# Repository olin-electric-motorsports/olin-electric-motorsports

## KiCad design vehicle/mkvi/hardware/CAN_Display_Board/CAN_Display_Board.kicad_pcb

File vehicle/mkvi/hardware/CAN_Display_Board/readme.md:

This repository contains the kicad files for the CAN Display Board that Ian, Peter, and Ahan created.

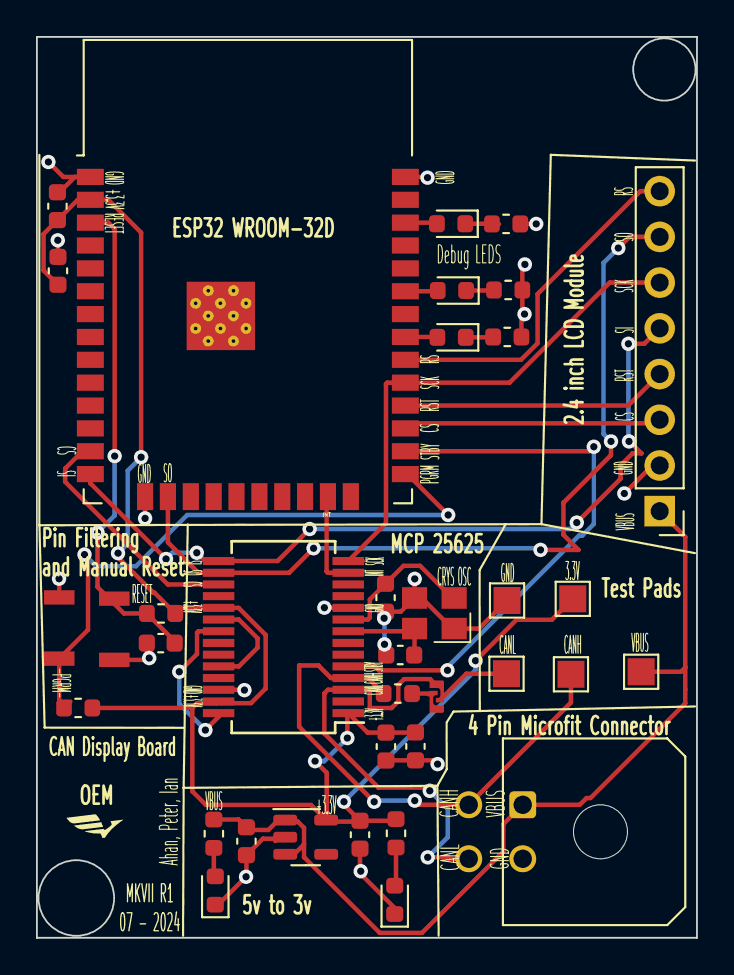
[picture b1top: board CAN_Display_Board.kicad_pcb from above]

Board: 2 copper layers, 36.7 x 50.0 mm, 36 parts (0 on the bottom side), 29 nets.

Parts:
+3.3V Test: TestPoint; TestPoint_Pad_1.5x1.5mm
C1, C2, C3, C4: C_0.1uF; C_0603_1608Metric
C5: C_10uF; C_0603_1608Metric
C6, C7: C_1uF; C_0603_1608Metric
C8, C9: C_30pF; C_0603_1608Metric
CANH Test: TestPoint; TestPoint_Pad_1.5x1.5mm
CANL Test: TestPoint; TestPoint_Pad_1.5x1.5mm
D1, D2, D3, D4, D5: LED; LED_0603_1608Metric
GND : TestPoint; TestPoint_Pad_1.5x1.5mm
J1: Conn_01x08_Pin; PinHeader_1x08_P2.54mm_Vertical
J2: MicroFit_RA_4
JP2: SolderJumper_2_Open; SolderJumper-2_Open_Hooks0.8x1.8mm
R1, R3: R_10K; R_0603_1608Metric
R2: R_120; R_0603_1608Metric
R4, R5, R6, R7, R8: R_220; R_0603_1608Metric
SW1, SW2: SW_Push_SPST_NO; SW_B3U-1000P_4.2x1.7mm
U1: AP2112K-3.3; SOT-23-5
U2: ESP32-WROOM-32D
U3: MCP25625-x-SS; SSOP-28_5.3x10.2mm_P0.65mm
VBUS Test: TestPoint; TestPoint_Pad_1.5x1.5mm
Y1: Crystal_TXC7M

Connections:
+3.3V: +3.3V Test.1, C1.1, C2.1, C3.1, C4.1, C7.1, R1.1, R3.2, R5.1, U1.5 (VOUT), U2.2 (VDD), U3.1 (VIO), U3.19 (VDD), U3.27 (VDDA)
/1O0: R3.1, SW2.2, U2.25 (IO0)
/CANH: CANH Test.1, J2.3, R2.1, U3.4 (CANH)
/CANL: CANL Test.1, J2.4, JP2.1 (A), U3.3 (CANL)
/CS: U2.13 (IO14), U3.17 (~CS)
/EN: C5.1, R1.2, SW1.2, U2.3 (EN)
/INT: U2.23 (IO15), U3.13 (~INT)
/LCD CS: J1.3, U2.27 (IO16)
/LCD RS: J1.8, U2.30 (IO18)
/LCD RST: J1.4, U2.28 (IO17)
/SCK: J1.6, U2.29 (IO5), U3.14 (SCK)
/SI: J1.5, U2.14 (IO12), U3.15 (SI)
/SO: J1.7, U2.16 (IO13), U3.16 (SO)
/STBY: U2.26 (IO4), U3.5 (STBY)
GND: C1.2, C2.2, C3.2, C4.2, C5.2, C6.2, C7.2, C8.1, C9.2, D1.1 (K), D2.1 (K), GND.1, J1.2, J2.2, R6.2, R7.2, R8.2, SW1.1, SW2.1, U1.2 (GND), U2.1 (GND), U2.15 (GND), U2.38 (GND), U2.39 (GND), U3.10 (GND), U3.26 (VSS), Y1.2, Y1.4
unnamed: D1.2 (A), R4.2
unnamed: D2.2 (A), R5.2
unnamed: D3.2 (A), U2.31 (IO19)
unnamed: D3.1 (K), R6.1
unnamed: D4.2 (A), U2.33 (IO21)
unnamed: D4.1 (K), R7.1
unnamed: D5.2 (A), U2.36 (IO22)
unnamed: D5.1 (K), R8.1
unnamed: JP2.2 (B), R2.2
unnamed: C8.2, U3.9 (OSC1), Y1.1
unnamed: C9.1, U3.8 (OSC2), Y1.3
unnamed: U3.21 (RxCAN), U3.28 (RXD)
unnamed: U3.20 (TxCAN), U3.24 (TXD)
VBUS: C6.1, J1.1, J2.1, R4.1, U1.1 (VIN), U1.3 (EN), VBUS Test.1

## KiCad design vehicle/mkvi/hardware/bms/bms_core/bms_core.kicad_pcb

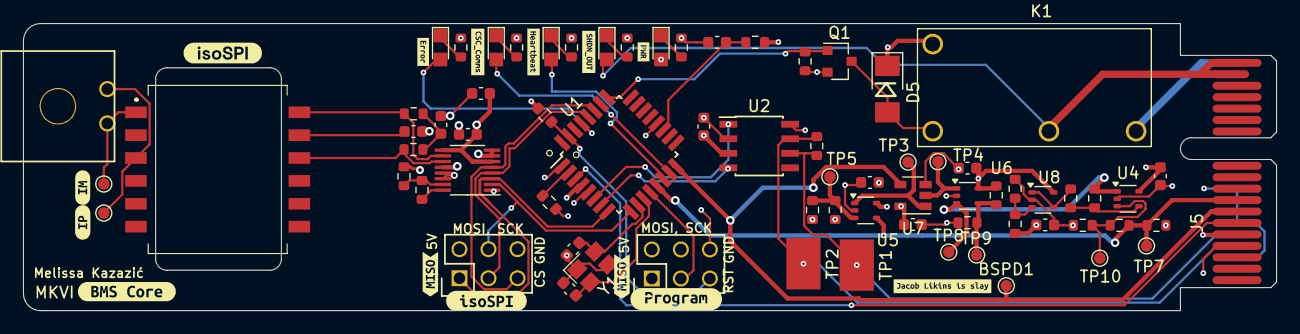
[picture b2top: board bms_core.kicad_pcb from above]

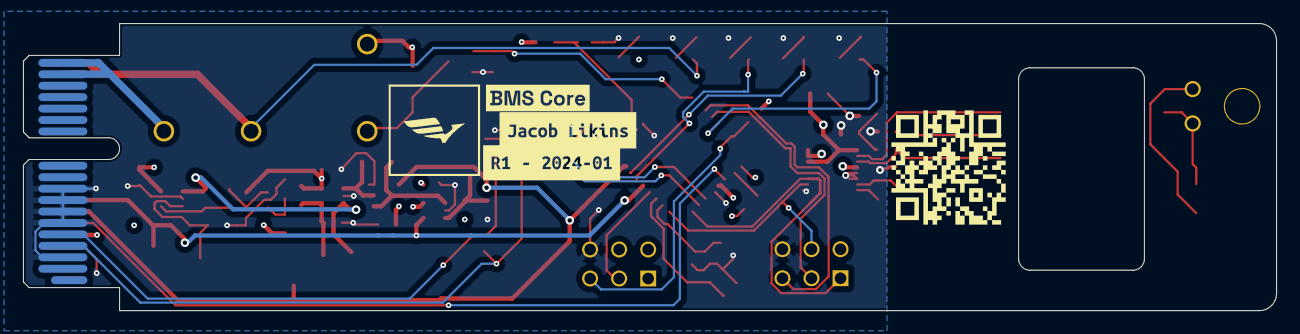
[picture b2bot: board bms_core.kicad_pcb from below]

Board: 4 copper layers, 109.6 x 25.1 mm, 90 parts (4 on the bottom side), 50 nets.

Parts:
BSPD1: BSPD_CURRENT_THRESH; TestPoint_Pad_D1.0mm
C1, C4, C6, C9, C10, C11, C12, C13: C_0.1uF; C_0603
C2: C_100pF; C_0603
C3, C5: C_30pF; C_0603
C7, C8: C_10nF; C_0603
D1: LED_AMBER; CHIPLED_0805
D2: LED_GREEN; CHIPLED_0805
D3: LED_RED; CHIPLED_0805
D4: LED_WHITE; CHIPLED_0805
D5: D_Zener_18V_SMBJ5355B-TP; DO-214AA
D6: LED_BLUE; CHIPLED_0805
IM1: TP_1mm; TestPoint_Pad_D1.0mm
IP1: TP_1mm; TestPoint_Pad_D1.0mm
J1, J2: CONN_02x03; Pin_Header_Straight_2x03
J3: MicroFit_RA_2
J5: CONN_pcie_x1; pcie_x1
K1: Relay_G5Q-1A4-DC5; Relay_SPST_OMRON-G5Q-1A4_OEM
Q1: SSM3K333R; SOT-23F
QR*****: hw.oem.to/QR_6_BMS-CORE_1; QR_6_BMS-CORE_1
R1, R3, R21, R22, R23: 1KR; R_0603
R2: R_100; R_0603
R4: 100R; R_0603
R5: R_120_DNP; R_0603
R6, R7, R12, R13, R14, R15, R16, R19, R24, R25: R_10K; R_0603
R8, R9, R18: R_1K; R_0603
R10, R11: R_60.4; R_0603
R17: R_1M; R_0603
R20: R_576; R_0603
T1: HM2112ZNLT
TP1: CANL1; Test_Point_SMD
TP2: CANH1; Test_Point_SMD
TP3: GND_SHORT; TestPoint_Pad_D1.0mm
TP4: CURRENT_TRIP; TestPoint_Pad_D1.0mm
TP5: V_GND_THRESHOLD; TestPoint_Pad_D1.0mm
TP7: VOUT; TestPoint_Pad_D1.0mm
TP8: VSTATUS; TestPoint_Pad_D1.0mm
TP9: VTRIP; TestPoint_Pad_D1.0mm
TP10: TP_1mm; TestPoint_Pad_D1.0mm
U1: ATMEGA64M1; TQFP-32_7x7mm_Pitch0.8mm
U2: MAX33011EASA; SOIC-8_3.9x4.9mm_Pitch1.27mm_OEM
U3: LTC6820HMS; MSOP-16_3x4mm_P0.5mm
U4, U5, U6, U8: MCP6001; SOT-353_SC-70-5
U7: SN74LVC1G32DBVR; SOT-23-5_OEM
Y1: Crystal_16MHz_18pF; Crystal_SMD_FA238
kibuzzard-63B930AD, kibuzzard-63B930AD#2: G***; kibuzzard-63B930AD
kibuzzard-63B9305B: G***; kibuzzard-63B9305B
kibuzzard-63B93076: G***; kibuzzard-63B93076
kibuzzard-63BB8A3F: G***; kibuzzard-63BB8A3F
kibuzzard-63BB8A53: G***; kibuzzard-63BB8A53
kibuzzard-63BF4A21: G***; kibuzzard-63BF4A21
kibuzzard-63BF43E2: G***; kibuzzard-63BF43E2
kibuzzard-63BF57C4: G***; kibuzzard-63BF57C4
kibuzzard-671D4F66: G***; kibuzzard-671D4F66
kibuzzard-671D5265: G***; kibuzzard-671D5265
kibuzzard-671D5273: G***; kibuzzard-671D5273
kibuzzard-671D5279: G***; kibuzzard-671D5279
kibuzzard-671FF8D2: G***; kibuzzard-671FF8D2
kibuzzard-671FF51F: G***; kibuzzard-671FF51F
kibuzzard-67240C9D: G***; kibuzzard-67240C9D
kibuzzard-67240CB0: G***; kibuzzard-67240CB0

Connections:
+5V: C1.1, C4.1, C6.1, C9.1, C10.1, C11.1, C12.1, C13.1, D4.2 (A), D5.1 (K), J1.2, J2.2, J5.B5 (5V), K1.5, R2.1, R6.1, R12.2, R17.1, R19.2, R24.1, U1.4 (VCC), U2.3 (VDD), U3.6 (VDDS), U3.7 (POL), U3.8 (PHA), U3.9 (VDD), U3.12 (MSTR), U4.5 (V+), U5.5 (V+), U6.5 (V+), U7.5 (VCC), U8.5 (V+)
/BMS_RELAY_DRIVE: Q1.1 (G), R7.2, U1.25 ((PCINT15/D2A/AMP2+)PC7)
/BSPD Current Sensor Trigger/CURRENT_TRIP: TP4.1, U6.1, U7.2 (in)
/BSPD Current Sensor Trigger/GND_SHORT: TP3.1, U5.1, U7.1 (in)
/BSPD Current Sensor Trigger/VSTATUS: R15.2, TP8.1, U4.1, U6.3 (+)
/BSPD Current Sensor Trigger/VTRIP: R19.1, R20.1, TP9.1, U6.4 (-)
/BSPD Current Sensor Trigger/V_GND_THRESHOLD: R17.2, R18.1, TP5.1, U5.3 (+)
/BSPD_CURRENT_THRESH: BSPD1.1, J5.B7 (io_3), U1.16 ((PCINT2/ADC5/INT1/ACMPN0)PB2), U7.4 (out)
/CANH: J5.A4 (CAN+), R5.1, TP2.1, U2.7 (CANH)
/CANL: J5.A5 (CAN-), R5.2, TP1.1, U2.6 (CANL)
/CSC_Comms: D2.2 (A), U1.15 ((PCINT23/ACMP0)PD7)
/Error: D3.2 (A), U1.29 ((PCINT16/PSCOUT0A)PD0)
/FAN_PWM: J5.B6 (io_1), U1.3 ((PCINT9/PSCIN1/OC1B/~SS_A)PC1)
/Heartbeat: D1.2 (A), U1.14 ((PCINT22/ADC3/INT0/ACMPN2)PD6)
/IM: IM1.1, J3.1, T1.1
/IP: IP1.1, J3.2, T1.3
/ISO_CS: J2.5, U1.27 ((PCINT6/ADC7/PSCOUT1B)PB6), U3.5 (~CS)
/ISO_MISO: J2.1, U1.8 ((PCINT0/MISO/PSCOUT2A)PB0), U3.3 (MISO)
/ISO_MOSI: J2.4, U1.9 ((PCINT1/MOSI/PSCOUT2B)PB1), U3.2 (MOSI)
/ISO_SCK: J2.3, U1.28 ((PCINT7/ADC4/SCK/PSCOUT0B)PB7), U3.4 (SCK)
/MISO: J1.1, U1.1 ((PCINT18/PSCIN2/OC1A/MISO_A)PD2)
/MOSI: J1.4, R4.1
/RESET: J1.5, R6.2, U1.31 ((PCINT24/OCD/~RESET)PE0)
/RXCAN: U1.7 ((PCINT11/T1/ICP1B/RXCAN)PC3), U2.4 (RXD)
/SCK: J1.3, U1.12 ((PCINT20/ADC1/RXD/RXLIN/ICP1A/SCK_A)PD4)
/SHDN_IN: J5.A17 (SHDN_IN/io_22), J5.A18 (SHDN_IN/io_24), K1.3
/SHDN_OUT: D6.2 (A), J5.B17 (SHDN_OUT/io_23), J5.B18 (SHDN_OUT/io_25), K1.2
/TXCAN: U1.6 ((PCINT10/T0/TXCAN)PC2), U2.1 (TXD)
/VOUT_CURRENT_SENSE: J5.B8 (io_5), R12.1, R13.1, TP7.1, U1.13 ((PCINT21/ADC2/ACMP2)PD5), U5.4 (-)
GND: C1.2, C2.2, C3.2, C4.2, C5.2, C6.2, C7.2, C8.2, C9.2, C10.2, C11.2, C12.2, C13.2, J1.6, J2.6, J5.A3 (GND), J5.A6 (io_0), J5.A7 (io_2), J5.A8 (io_4), J5.A9 (io_6), J5.B4 (GND), Q1.2 (S), R1.2, R3.2, R7.1, R9.2, R14.1, R18.2, R20.2, R21.2, R22.2, R23.2, R25.2, U1.5 (GND), U1.20 (AGND), U2.2 (VSS), U2.8 (STBY), U3.1 (EN), U3.13 (SLOW), U3.14 (GND), U4.2 (V-), U5.2 (V-), U6.2 (V-), U7.3 (GND), U8.2 (V-), Y1.2, Y1.4
unnamed: C7.1, R10.2, R11.1
unnamed: C8.1, T1.11
unnamed: D1.1 (K), R1.1
unnamed: D2.1 (K), R3.1
unnamed: D3.1 (K), R21.1
unnamed: D4.1 (K), R22.1
unnamed: D5.2 (A), K1.1, Q1.3 (D)
unnamed: D6.1 (K), R23.1
unnamed: R4.2, U1.2 ((PCINT19/TXD/TXLIN/OC0A/~SS/MOSI_A)PD3)
unnamed: C5.1, U1.10 ((PCINT25/OC0B/XTAL1)PE1), Y1.3
unnamed: C3.1, U1.11 ((PCINT26/ADC0/XTAL2)PE2), Y1.1
unnamed: C2.1, R2.2, U1.19 (AVCC)
unnamed: R8.1, U3.16 (IBIAS)
unnamed: R8.2, R9.1, U3.15 (ICMP)
unnamed: R10.1, T1.12, U3.10 (IM)
unnamed: R11.2, T1.10, U3.11 (IP)
unnamed: R13.2, R14.2, TP10.1, U4.3 (+)
unnamed: R15.1, R16.2, U4.4 (-)
unnamed: R24.2, R25.1, U8.3 (+)
unnamed: R16.1, U8.1, U8.4 (-)

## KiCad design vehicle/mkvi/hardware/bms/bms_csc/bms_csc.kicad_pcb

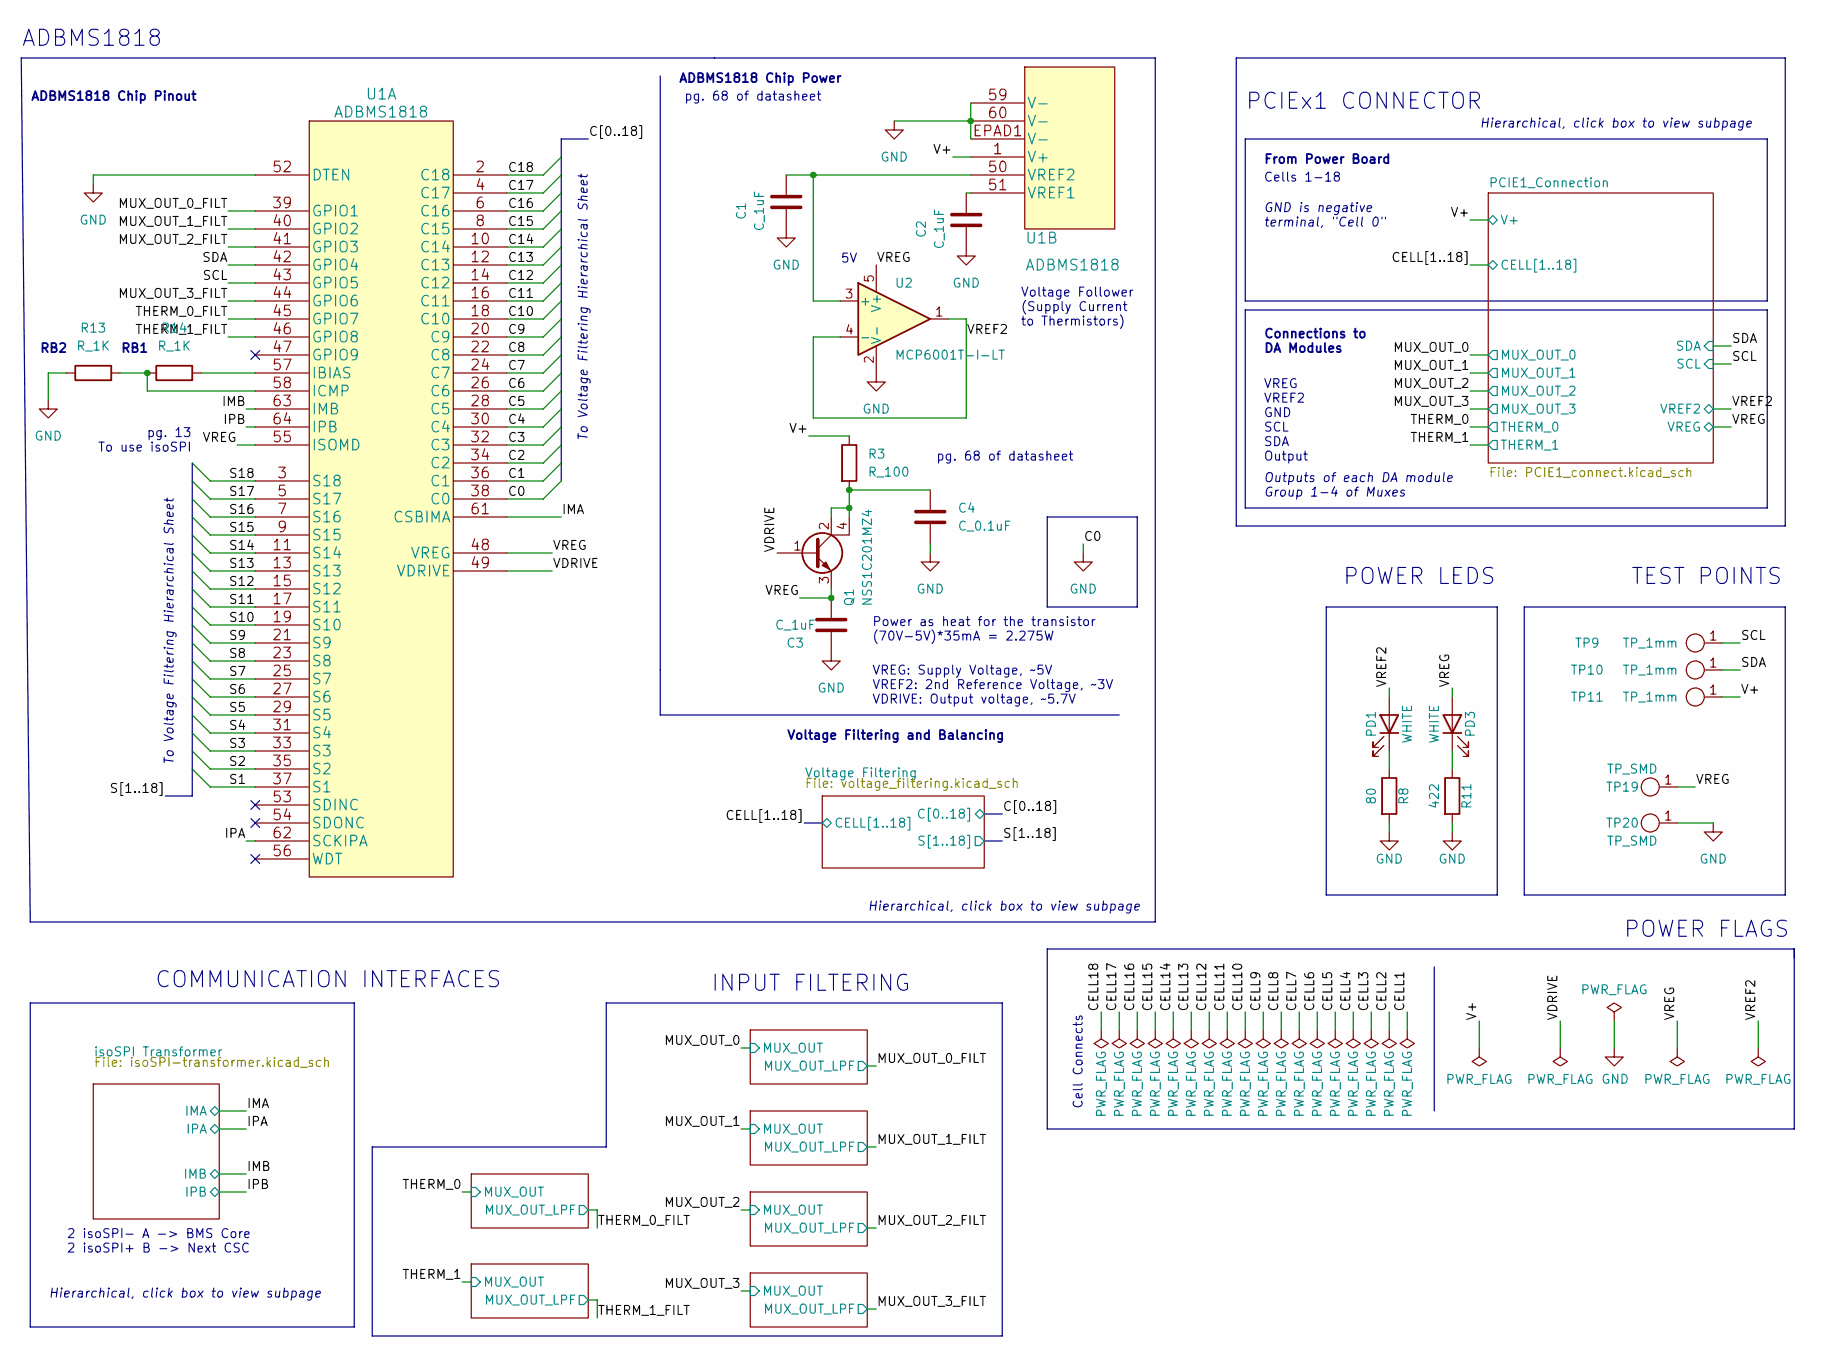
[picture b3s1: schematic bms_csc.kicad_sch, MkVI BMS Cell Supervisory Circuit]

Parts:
C1, C2, C3: C_1uF; C_0603; MPN CL10B105KA8NNNC
C4: C_0.1uF; C_0603; MPN CL10B104KB8NNWC
PD1, PD3: WHITE; LED_0402_1005Metric; MPN B1701TW--20P000314U1930
Q1: NSS1C201MZ4; SOT-223; MPN NSS1C201MZ4
R3: R_100; R_2512_OEM; MPN RMCF0603FT100R
R8: 80; R_0603; MPN RMCF0603FT1K00
R11: 422; R_0603; MPN RMCF0603FT1K00
R13, R14: R_1K; R_0603; MPN RMCF0603FT1K00
TP9, TP10, TP11: TP_1mm; TestPoint_Pad_D1.0mm
TP19, TP20: TP_SMD; Test_Point_SMD; MPN 5019
U1: ADBMS1818; LQFP-64-1EP_12x12_P0.5; MPN ADBMS1818
U2: MCP6001T-I-LT; SOT-353_SC-70-5; MPN MCP6001T-I/OT

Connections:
/C1: U1.36 (C1); also elsewhere on the board
/C2: U1.34 (C2); also elsewhere on the board
/C3: U1.32 (C3); also elsewhere on the board
/C4: U1.30 (C4); also elsewhere on the board
/C5: U1.28 (C5); also elsewhere on the board
/C6: U1.26 (C6); also elsewhere on the board
/C7: U1.24 (C7); also elsewhere on the board
/C8: U1.22 (C8); also elsewhere on the board
/C9: U1.20 (C9); also elsewhere on the board
/C10: U1.18 (C10); also elsewhere on the board
/C11: U1.16 (C11); also elsewhere on the board
/C12: U1.14 (C12); also elsewhere on the board
/C13: U1.12 (C13); also elsewhere on the board
/C14: U1.10 (C14); also elsewhere on the board
/C15: U1.8 (C15); also elsewhere on the board
/C16: U1.6 (C16); also elsewhere on the board
/C17: U1.4 (C17); also elsewhere on the board
/C18: U1.2 (C18); also elsewhere on the board
/IMA: U1.61 (CSBIMA); also elsewhere on the board
/IMB: U1.63 (IMB); also elsewhere on the board
/IPA: U1.62 (SCKIPA); also elsewhere on the board
/IPB: U1.64 (IPB); also elsewhere on the board
/MUX_OUT_0_FILT: U1.39 (GPIO1); also elsewhere on the board
/MUX_OUT_1_FILT: U1.40 (GPIO2); also elsewhere on the board
/MUX_OUT_2_FILT: U1.41 (GPIO3); also elsewhere on the board
/MUX_OUT_3_FILT: U1.44 (GPIO6); also elsewhere on the board
/S1: U1.37 (S1); also elsewhere on the board
/S2: U1.35 (S2); also elsewhere on the board
/S3: U1.33 (S3); also elsewhere on the board
/S4: U1.31 (S4); also elsewhere on the board
/S5: U1.29 (S5); also elsewhere on the board
/S6: U1.27 (S6); also elsewhere on the board
/S7: U1.25 (S7); also elsewhere on the board
/S8: U1.23 (S8); also elsewhere on the board
/S9: U1.21 (S9); also elsewhere on the board
/S10: U1.19 (S10); also elsewhere on the board
/S11: U1.17 (S11); also elsewhere on the board
/S12: U1.15 (S12); also elsewhere on the board
/S13: U1.13 (S13); also elsewhere on the board
/S14: U1.11 (S14); also elsewhere on the board
/S15: U1.9 (S15); also elsewhere on the board
/S16: U1.7 (S16); also elsewhere on the board
/S17: U1.5 (S17); also elsewhere on the board
/S18: U1.3 (S18); also elsewhere on the board
/SCL: TP9.1, U1.43 (GPIO5); also elsewhere on the board
/SDA: TP10.1, U1.42 (GPIO4); also elsewhere on the board
/THERM_0_FILT: U1.45 (GPIO7); also elsewhere on the board
/THERM_1_FILT: U1.46 (GPIO8); also elsewhere on the board
/V+: R3.1, TP11.1, U1.1 (V+); also elsewhere on the board
/VDRIVE: Q1.1 (B), U1.49 (VDRIVE)
/VREF2: PD1.2 (A), U2.1, U2.4 (-); also elsewhere on the board
/VREG: C3.2, PD3.2 (A), Q1.3 (E), TP19.1, U1.48 (VREG), U1.55 (ISOMD), U2.5 (V+); also elsewhere on the board
unnamed: C4.1, Q1.2 (C), Q1.4 (C), R3.2
unnamed: PD1.1 (K), R8.1
unnamed: PD3.1 (K), R11.1
unnamed: R14.2, U1.57 (IBIAS)
unnamed: R13.2, R14.1, U1.58 (ICMP)
unnamed: C2.2, U1.51 (VREF1)
unnamed: C1.2, U1.50 (VREF2), U2.3 (+)

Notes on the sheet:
RB2
Hierarchical, click box to view subpage
INPUT FILTERING
From Power Board
Power as heat for the transistor (70V-5V)*35mA = 2.275W
pg. 68 of datasheet
Cells 1-18
ADBMS1818 Chip Pinout
Outputs of each DA module Group 1-4 of Muxes
2 isoSPI- A -> BMS Core 2 isoSPI+ B -> Next CSC
COMMUNICATION INTERFACES
pg. 13 To use isoSPI
Voltage Filtering and Balancing
Voltage Follower (Supply Current to Thermistors)
ADBMS1818 Chip Power
VREG VREF2 GND SCL SDA Output
VREG: Supply Voltage, ~5V VREF2: 2nd Reference Voltage, ~3V VDRIVE: Output voltage, ~5.7V
Connections to DA Modules
ADBMS1818
Cell Connects
POWER FLAGS
PCIEx1 CONNECTOR
RB1
POWER LEDS
GND is negative terminal, "Cell 0"
To Voltage Filtering Hierarchical Sheet
TEST POINTS

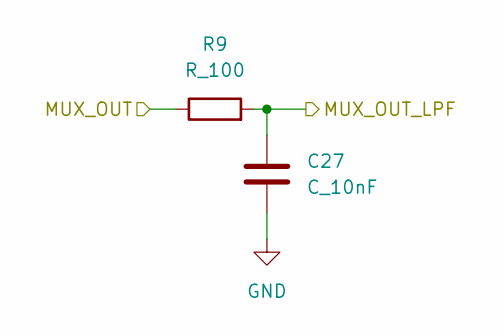
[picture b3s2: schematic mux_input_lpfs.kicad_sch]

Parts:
C27: C_10nF; C_0603; MPN CL10B104KB8NNWC
R9: R_100; R_0603; MPN RMCF0603FT100R

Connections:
/MUX_OUT_0: R9.1; also elsewhere on the board
/MUX_OUT_0_FILT: C27.1, R9.2; also elsewhere on the board

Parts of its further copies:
C28, C29, C30, C31, C32: C_10nF; C_0603; MPN CL10B104KB8NNWC
R10, R12, R51, R52, R53: R_100; R_0603; MPN RMCF0603FT100R

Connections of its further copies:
/MUX_OUT_1: R10.1; also elsewhere on the board
/MUX_OUT_1_FILT: C28.1, R10.2; also elsewhere on the board
/MUX_OUT_2: R12.1; also elsewhere on the board
/MUX_OUT_2_FILT: C29.1, R12.2; also elsewhere on the board
/MUX_OUT_3: R51.1; also elsewhere on the board
/MUX_OUT_3_FILT: C30.1, R51.2; also elsewhere on the board
/THERM_0: R52.1; also elsewhere on the board
/THERM_0_FILT: C31.1, R52.2; also elsewhere on the board
/THERM_1: R53.1; also elsewhere on the board
/THERM_1_FILT: C32.1, R53.2; also elsewhere on the board

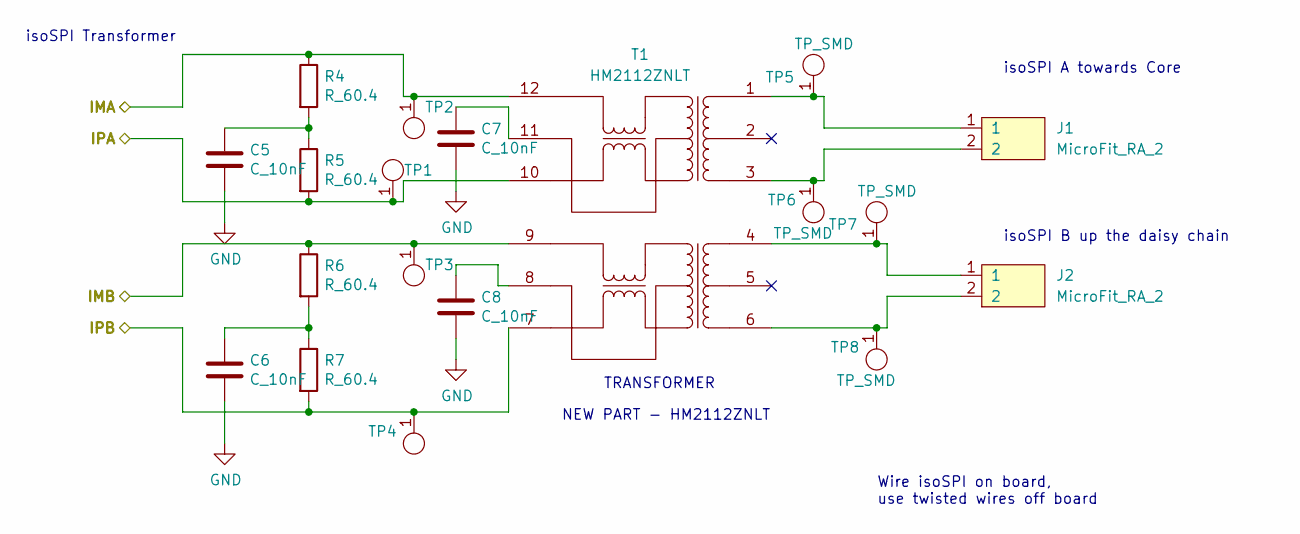
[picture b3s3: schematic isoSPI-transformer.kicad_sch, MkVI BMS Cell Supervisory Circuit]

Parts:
C5, C6, C7, C8: C_10nF; C_0603; MPN CL10B103KB8NNNC
J1, J2: MicroFit_RA_2; MPN 0436500201
R4, R5, R6, R7: R_60.4; R_0603; MPN RMCF0603FT60R4
T1: HM2112ZNLT; MPN HM2112ZNLT
TP1, TP2, TP3, TP4, TP5, TP6, TP7, TP8: TP_SMD; Test_Point_SMD; MPN 5019

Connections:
/IMA: R4.1, T1.12, TP2.1; also elsewhere on the board
/IMB: R6.1, T1.9, TP3.1; also elsewhere on the board
/IPA: R5.2, T1.10, TP1.1; also elsewhere on the board
/IPB: R7.2, T1.7, TP4.1; also elsewhere on the board
unnamed: C5.1, R4.2, R5.1
unnamed: C6.1, R6.2, R7.1
unnamed: C7.1, T1.11
unnamed: C8.1, T1.8
unnamed: J1.1, T1.1, TP5.1
unnamed: J1.2, T1.3, TP6.1
unnamed: J2.1, T1.4, TP7.1
unnamed: J2.2, T1.6, TP8.1

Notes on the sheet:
isoSPI B up the daisy chain
TRANSFORMER
isoSPI Transformer
NEW PART - HM2112ZNLT
isoSPI A towards Core
Wire isoSPI on board, use twisted wires off board

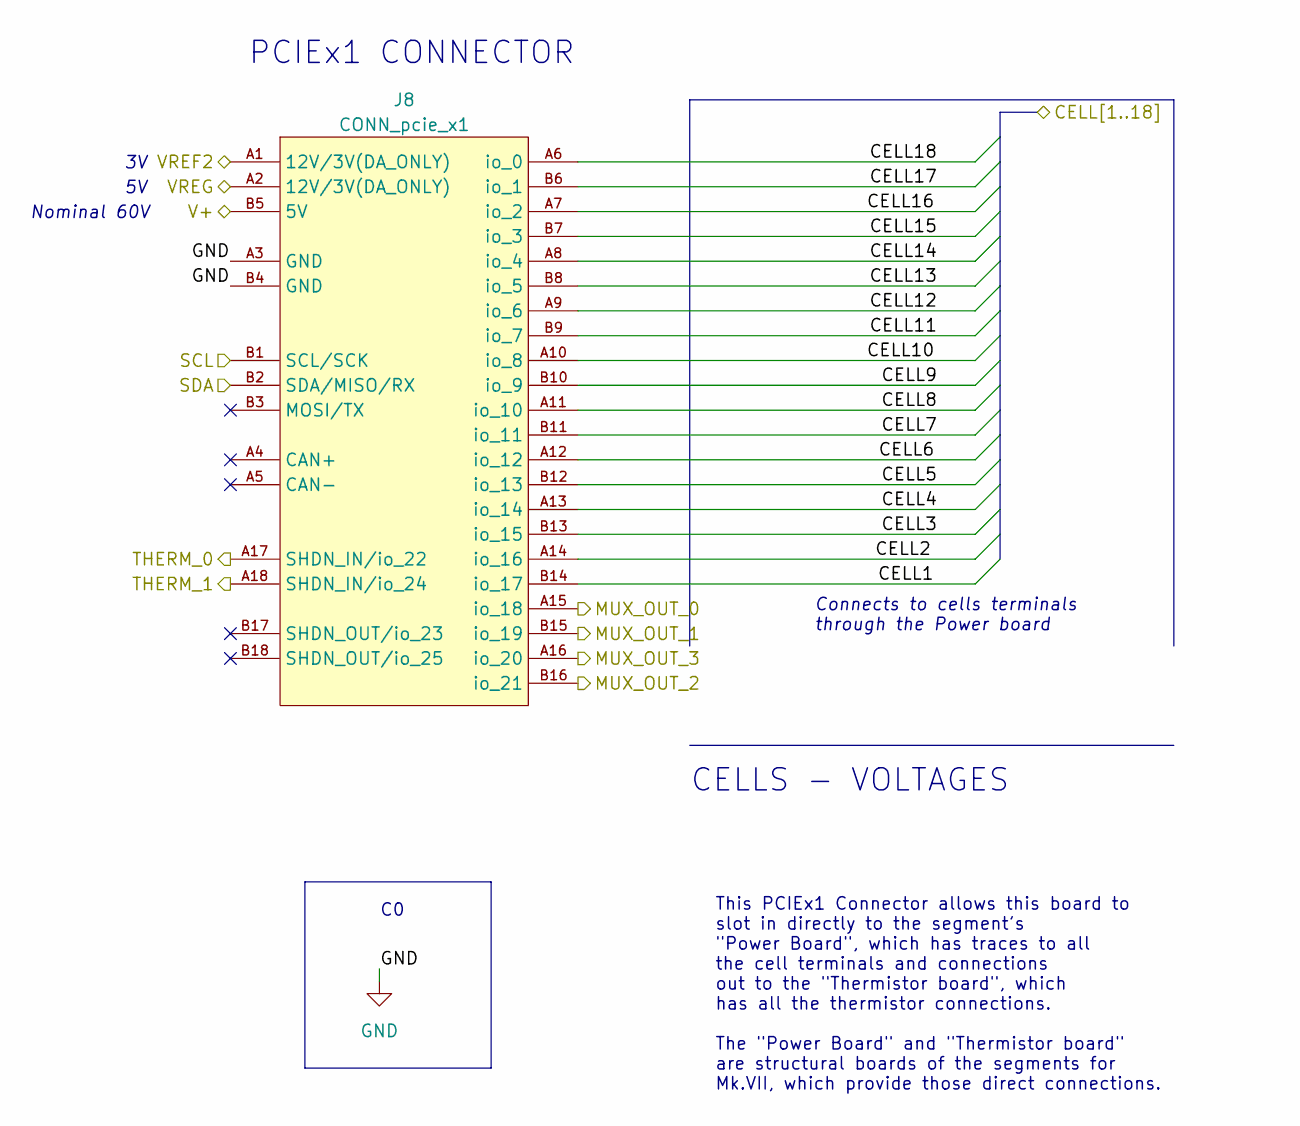
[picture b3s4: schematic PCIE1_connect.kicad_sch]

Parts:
J8: CONN_pcie_x1; pcie_x1

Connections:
/CELL1: J8.B14 (io_17); also elsewhere on the board
/CELL2: J8.A14 (io_16); also elsewhere on the board
/CELL3: J8.B13 (io_15); also elsewhere on the board
/CELL4: J8.A13 (io_14); also elsewhere on the board
/CELL5: J8.B12 (io_13); also elsewhere on the board
/CELL6: J8.A12 (io_12); also elsewhere on the board
/CELL7: J8.B11 (io_11); also elsewhere on the board
/CELL8: J8.A11 (io_10); also elsewhere on the board
/CELL9: J8.B10 (io_9); also elsewhere on the board
/CELL10: J8.A10 (io_8); also elsewhere on the board
/CELL11: J8.B9 (io_7); also elsewhere on the board
/CELL12: J8.A9 (io_6); also elsewhere on the board
/CELL13: J8.B8 (io_5); also elsewhere on the board
/CELL14: J8.A8 (io_4); also elsewhere on the board
/CELL15: J8.B7 (io_3); also elsewhere on the board
/CELL16: J8.A7 (io_2); also elsewhere on the board
/CELL17: J8.B6 (io_1); also elsewhere on the board
/CELL18: J8.A6 (io_0); also elsewhere on the board
/MUX_OUT_0: J8.A15 (io_18); also elsewhere on the board
/MUX_OUT_1: J8.B15 (io_19); also elsewhere on the board
/MUX_OUT_2: J8.B16 (io_21); also elsewhere on the board
/MUX_OUT_3: J8.A16 (io_20); also elsewhere on the board
/SCL: J8.B1 (SCL/SCK); also elsewhere on the board
/SDA: J8.B2 (SDA/MISO/RX); also elsewhere on the board
/THERM_0: J8.A17 (SHDN_IN/io_22); also elsewhere on the board
/THERM_1: J8.A18 (SHDN_IN/io_24); also elsewhere on the board
/V+: J8.B5 (5V); also elsewhere on the board
/VREF2: J8.A1 (12V/3V(DA_ONLY)); also elsewhere on the board
/VREG: J8.A2 (12V/3V(DA_ONLY)); also elsewhere on the board

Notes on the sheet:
This PCIEx1 Connector allows this board to slot in directly to the segment's "Power Board", which has traces to all the cell terminals and connections out to the "Thermistor board", which has all the thermistor connections. The "Power Board" and "Thermistor board" are structural boards of the segme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
CELLS - VOLTAGES
PCIEx1 CONNECTOR
Connects to cells terminals through the Power board
Nominal 60V

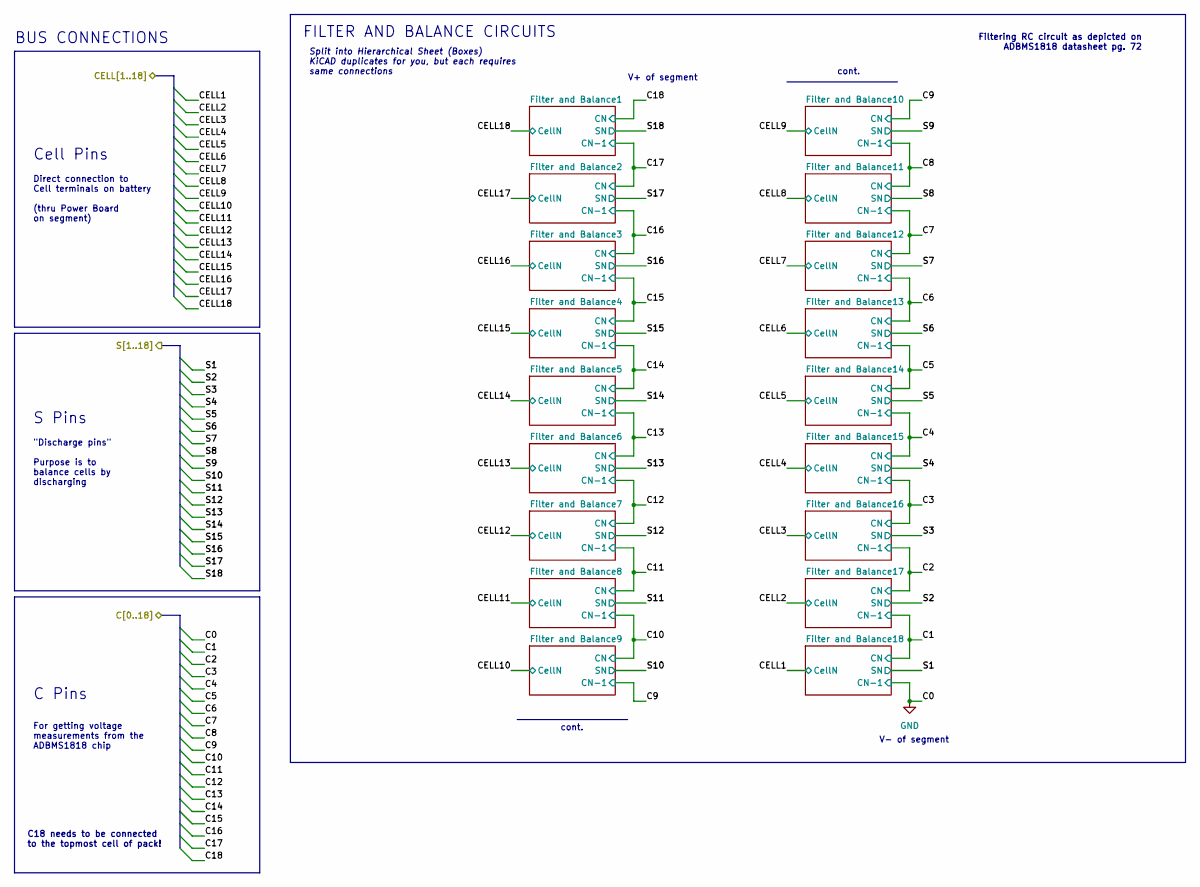
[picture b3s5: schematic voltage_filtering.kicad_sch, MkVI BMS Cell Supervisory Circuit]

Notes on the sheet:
BUS CONNECTIONS
C18 needs to be connected to the topmost cell of pack!
For getting voltage measurements from the ADBMS1818 chip
cont.
Cell Pins
Direct connection to Cell terminals on battery (thru Power Board on segment)
C Pins
V+ of segment
Filtering RC circuit as depicted on ADBMS1818 datasheet pg. 72
V- of segment
FILTER AND BALANCE CIRCUITS
S Pins
"Discharge pins" Purpose is to balance cells by discharging
Split into Hierarchical Sheet (Boxes) KiCAD duplicates for you, but each requires same connections

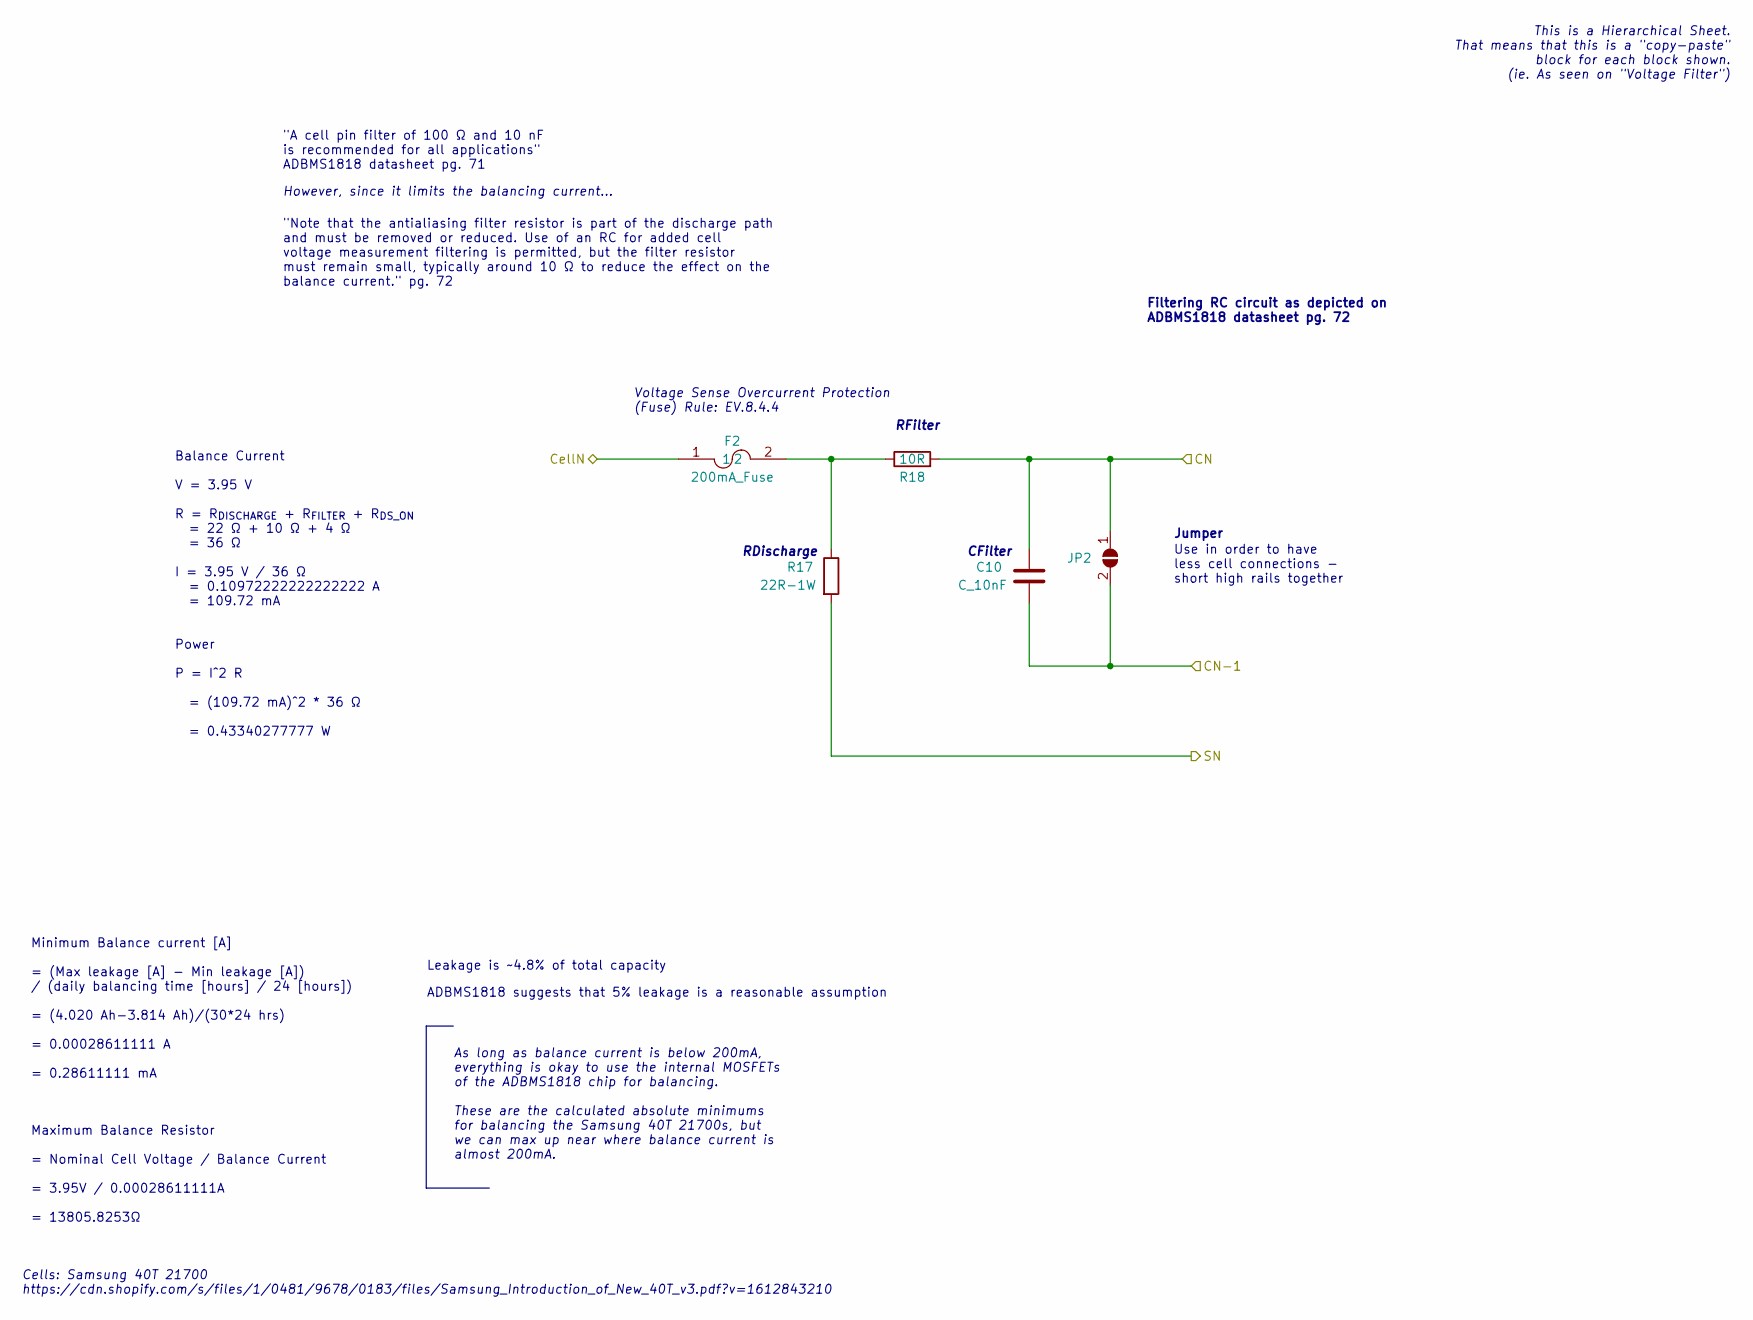
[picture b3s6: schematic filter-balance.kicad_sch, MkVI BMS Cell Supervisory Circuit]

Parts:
C10: C_10nF; C_0603; MPN CL10B103KB8NNNC
F2: 200mA_Fuse; Fuse_1206_3216Metric; MPN 0466.200NRHF
JP2: SolderJumper_2_Open; SolderJumper-2_P1.3mm_Open_TrianglePad1.0x1.5mm
R17: 22R-1W; R_2512_6332Metric; MPN 352022RJT
R18: 10R; R_0603; MPN SG73P1JTTD100J

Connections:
/C17: C10.2, JP2.2 (B); also elsewhere on the board
/C18: C10.1, JP2.1 (A), R18.2; also elsewhere on the board
/CELL18: F2.1; also elsewhere on the board
/S18: R17.2; also elsewhere on the board
unnamed: F2.2, R17.1, R18.1

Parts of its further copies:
C9, C11, C12, C13, C14, C15, C16, C17, C18, C19, C20, C21, C22, C23, C24, C25, C26: C_10nF; C_0603; MPN CL10B103KB8NNNC
F1, F3, F4, F5, F6, F7, F8, F9, F10, F11, F12, F13, F14, F15, F16, F17, F18: 200mA_Fuse; Fuse_1206_3216Metric; MPN 0466.200NRHF
JP1, JP3, JP4, JP5, JP6, JP7, JP8, JP9, JP10, JP11, JP12, JP13, JP14, JP15, JP16, JP17, JP18: SolderJumper_2_Open; SolderJumper-2_P1.3mm_Open_TrianglePad1.0x1.5mm
R15, R19, R21, R23, R25, R27, R29, R31, R33, R35, R37, R39, R41, R43, R45, R47, R49: 22R-1W; R_2512_6332Metric; MPN 352022RJT
R16, R20, R22, R24, R26, R28, R30, R32, R34, R36, R38, R40, R42, R44, R46, R48, R50: 10R; R_0603; MPN SG73P1JTTD100J

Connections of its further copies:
/C1: C25.2, C26.1, JP17.2 (B), JP18.1 (A), R50.2; also elsewhere on the board
/C2: C24.2, C25.1, JP16.2 (B), JP17.1 (A), R48.2; also elsewhere on the board
/C3: C23.2, C24.1, JP15.2 (B), JP16.1 (A), R46.2; also elsewhere on the board
/C4: C22.2, C23.1, JP14.2 (B), JP15.1 (A), R44.2; also elsewhere on the board
/C5: C21.2, C22.1, JP13.2 (B), JP14.1 (A), R42.2; also elsewhere on the board
/C6: C20.2, C21.1, JP12.2 (B), JP13.1 (A), R40.2; also elsewhere on the board
/C7: C19.2, C20.1, JP11.2 (B), JP12.1 (A), R38.2; also elsewhere on the board
/C8: C18.2, C19.1, JP10.2 (B), JP11.1 (A), R36.2; also elsewhere on the board
/C9: C17.2, C18.1, JP9.2 (B), JP10.1 (A), R34.2; also elsewhere on the board
/C10: C16.2, C17.1, JP8.2 (B), JP9.1 (A), R32.2; also elsewhere on the board
/C11: C15.2, C16.1, JP7.2 (B), JP8.1 (A), R30.2; also elsewhere on the board
/C12: C14.2, C15.1, JP6.2 (B), JP7.1 (A), R28.2; also elsewhere on the board
/C13: C13.2, C14.1, JP5.2 (B), JP6.1 (A), R26.2; also elsewhere on the board
/C14: C12.2, C13.1, JP4.2 (B), JP5.1 (A), R24.2; also elsewhere on the board
/C15: C9.2, C12.1, JP1.2 (B), JP4.1 (A), R22.2; also elsewhere on the board
/C16: C9.1, C11.2, JP1.1 (A), JP3.2 (B), R16.2; also elsewhere on the board
/C17: C11.1, JP3.1 (A), R20.2; also elsewhere on the board
/CELL1: F18.1; also elsewhere on the board
/CELL2: F17.1; also elsewhere on the board
/CELL3: F16.1; also elsewhere on the board
/CELL4: F15.1; also elsewhere on the board
/CELL5: F14.1; also elsewhere on the board
/CELL6: F13.1; also elsewhere on the board
/CELL7: F12.1; also elsewhere on the board
/CELL8: F11.1; also elsewhere on the board
/CELL9: F10.1; also elsewhere on the board
/CELL10: F9.1; also elsewhere on the board
/CELL11: F8.1; also elsewhere on the board
/CELL12: F7.1; also elsewhere on the board
/CELL13: F6.1; also elsewhere on the board
/CELL14: F5.1; also elsewhere on the board
/CELL15: F4.1; also elsewhere on the board
/CELL16: F1.1; also elsewhere on the board
/CELL17: F3.1; also elsewhere on the board
/S1: R49.2; also elsewhere on the board
/S2: R47.2; also elsewhere on the board
/S3: R45.2; also elsewhere on the board
/S4: R43.2; also elsewhere on the board
/S5: R41.2; also elsewhere on the board
/S6: R39.2; also elsewhere on the board
/S7: R37.2; also elsewhere on the board
/S8: R35.2; also elsewhere on the board
/S9: R33.2; also elsewhere on the board
/S10: R31.2; also elsewhere on the board
/S11: R29.2; also elsewhere on the board
/S12: R27.2; also elsewhere on the board
/S13: R25.2; also elsewhere on the board
/S14: R23.2; also elsewhere on the board
/S15: R21.2; also elsewhere on the board
/S16: R15.2; also elsewhere on the board
/S17: R19.2; also elsewhere on the board
unnamed: F1.2, R15.1, R16.1
unnamed: F3.2, R19.1, R20.1
unnamed: F4.2, R21.1, R22.1
unnamed: F5.2, R23.1, R24.1
unnamed: F6.2, R25.1, R26.1
unnamed: F7.2, R27.1, R28.1
unnamed: F8.2, R29.1, R30.1
unnamed: F9.2, R31.1, R32.1
unnamed: F10.2, R33.1, R34.1
unnamed: F11.2, R35.1, R36.1
unnamed: F12.2, R37.1, R38.1
unnamed: F13.2, R39.1, R40.1
unnamed: F14.2, R41.1, R42.1
unnamed: F15.2, R43.1, R44.1
unnamed: F16.2, R45.1, R46.1
unnamed: F17.2, R47.1, R48.1
unnamed: F18.2, R49.1, R50.1

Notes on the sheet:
RDischarge
Leakage is ~4.8% of total capacity
Use in order to have less cell connections - short high rails together
"A cell pin filter of 100 Ω and 10 nF is recommended for all applications" ADBMS1818 datasheet pg. 71
This is a Hierarchical Sheet. That means that this is a "copy-paste" block for each block shown. (ie. As seen on "Voltage Filter")
CFilter
"Note that the antialiasing filter resistor is part of the discharge path and must be removed or reduced. Use of an RC for added cell voltage measurement filtering is permitted, but the filter resistor must remain small, typically around 10 Ω to reduce the effect on the balance current." pg. 72
Maximum Balance Resistor = Nominal Cell Voltage / Balance Current = 3.95V / 0.00028611111A = 13805.8253Ω
However, since it limits the balancing current...
Minimum Balance current [A] = (Max leakage [A] - Min leakage [A]) / (daily balancing time [hours] / 24 [hours]) = (4.020 Ah-3.814 Ah)/(30*24 hrs) = 0.00028611111 A = 0.28611111 mA
ADBMS1818 suggests that 5% leakage is a reasonable assumption
Jumper
Voltage Sense Overcurrent Protection (Fuse) Rule: EV.8.4.4
As long as balance current is below 200mA, everything is okay to use the internal MOSFETs of the ADBMS1818 chip for balancing. These are the calculated absolute minimums for balancing the Samsung 40T 21700s, but we can max up near where balance current is almost 200mA.
Filtering RC circuit as depicted on ADBMS1818 datasheet pg. 72
RFilter
Balance Current V = 3.95 V R = R_{DISCHARGE} + R_{FILTER} + R_{DS_ON} = 22 Ω + 10 Ω + 4 Ω = 36 Ω I = 3.95 V / 36 Ω = 0.10972222222222222 A = 109.72 mA Power P = I^2 R = (109.72 mA)^2 * 36 Ω = 0.43340277777 W
Cells: Samsung 40T 21700 https://cdn.shopify.com/s/files/1/0481/9678/0183/files/Samsung_Introduction_of_New_40T_v3.pdf?v=1612843210

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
